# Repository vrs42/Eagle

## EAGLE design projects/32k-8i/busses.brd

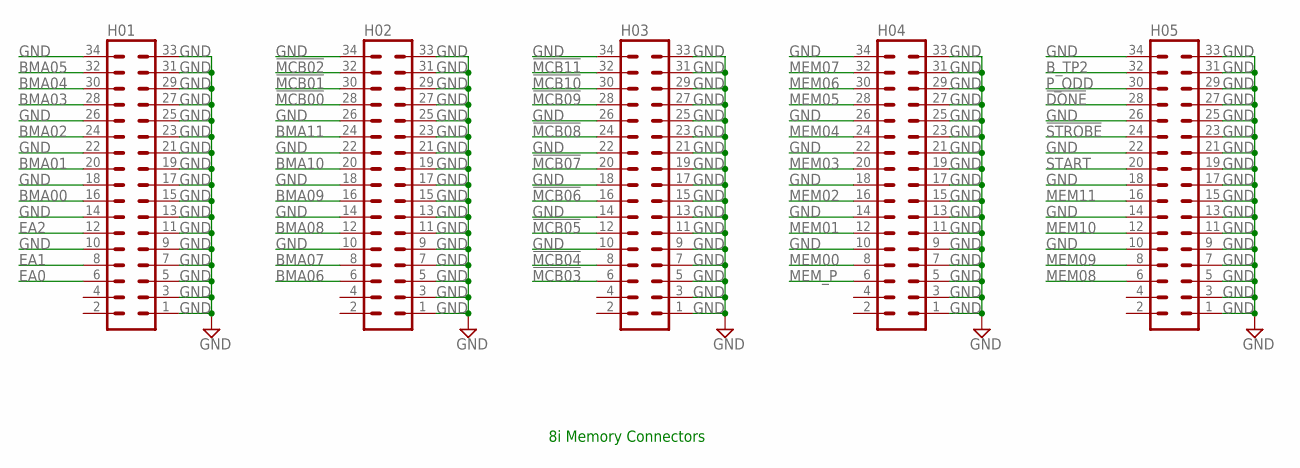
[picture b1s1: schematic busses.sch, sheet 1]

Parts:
H01, H02, H03, H04, H05: MA17-2

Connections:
!DONE: H05.28
!MCB00: H02.28; also elsewhere on the board
!MCB01: H02.30; also elsewhere on the board
!MCB02: H02.32; also elsewhere on the board
!MCB03: H03.6; also elsewhere on the board
!MCB04: H03.8; also elsewhere on the board
!MCB05: H03.12; also elsewhere on the board
!MCB06: H03.16; also elsewhere on the board
!MCB07: H03.20; also elsewhere on the board
!MCB08: H03.24; also elsewhere on the board
!MCB09: H03.28; also elsewhere on the board
!MCB10: H03.30; also elsewhere on the board
!MCB11: H03.32; also elsewhere on the board
!STROBE: H05.24
BMA00: H01.16
BMA01: H01.20
BMA02: H01.24
BMA03: H01.28
BMA04: H01.30
BMA05: H01.32
BMA06: H02.6
BMA07: H02.8
BMA08: H02.12
BMA09: H02.16
BMA10: H02.20
BMA11: H02.24
B_TP2: H05.32
EA0: H01.6; also elsewhere on the board
EA1: H01.8; also elsewhere on the board
EA2: H01.12; also elsewhere on the board
GND: H01.1, H01.3, H01.5, H01.7, H01.9, H01.10, H01.11, H01.13, H01.14, H01.15, H01.17, H01.18, H01.19, H01.21, H01.22, H01.23, H01.25, H01.26, H01.27, H01.29, H01.31, H01.33, H01.34, H02.1, H02.3, H02.5, H02.7, H02.9, H02.10, H02.11, H02.13, H02.14, H02.15, H02.17, H02.18, H02.19, H02.21, H02.22, H02.23, H02.25, H02.26, H02.27, H02.29, H02.31, H02.33, H02.34, H03.1, H03.3, H03.5, H03.7, H03.9, H03.10, H03.11, H03.13, H03.14, H03.15, H03.17, H03.18, H03.19, H03.21, H03.22, H03.23, H03.25, H03.26, H03.27, H03.29, H03.31, H03.33, H03.34, H04.1, H04.3, H04.5, H04.7, H04.9, H04.10, H04.11, H04.13, H04.14, H04.15, H04.17, H04.18, H04.19, H04.21, H04.22, H04.23, H04.25, H04.26, H04.27, H04.29, H04.31, H04.33, H04.34, H05.1, H05.3, H05.5, H05.7, H05.9, H05.10, H05.11, H05.13, H05.14, H05.15, H05.17, H05.18, H05.19, H05.21, H05.22, H05.23, H05.25, H05.26, H05.27, H05.29, H05.31, H05.33, H05.34; also elsewhere on the board
MEM00: H04.8; also elsewhere on the board
MEM01: H04.12; also elsewhere on the board
MEM02: H04.16; also elsewhere on the board
MEM03: H04.20; also elsewhere on the board
MEM04: H04.24; also elsewhere on the board
MEM05: H04.28; also elsewhere on the board
MEM06: H04.30; also elsewhere on the board
MEM07: H04.32; also elsewhere on the board
MEM08: H05.6; also elsewhere on the board
MEM09: H05.8; also elsewhere on the board
MEM10: H05.12; also elsewhere on the board
MEM11: H05.16; also elsewhere on the board
MEM_P: H04.6
P_ODD: H05.30
START: H05.20

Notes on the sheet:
8i Memory Connectors

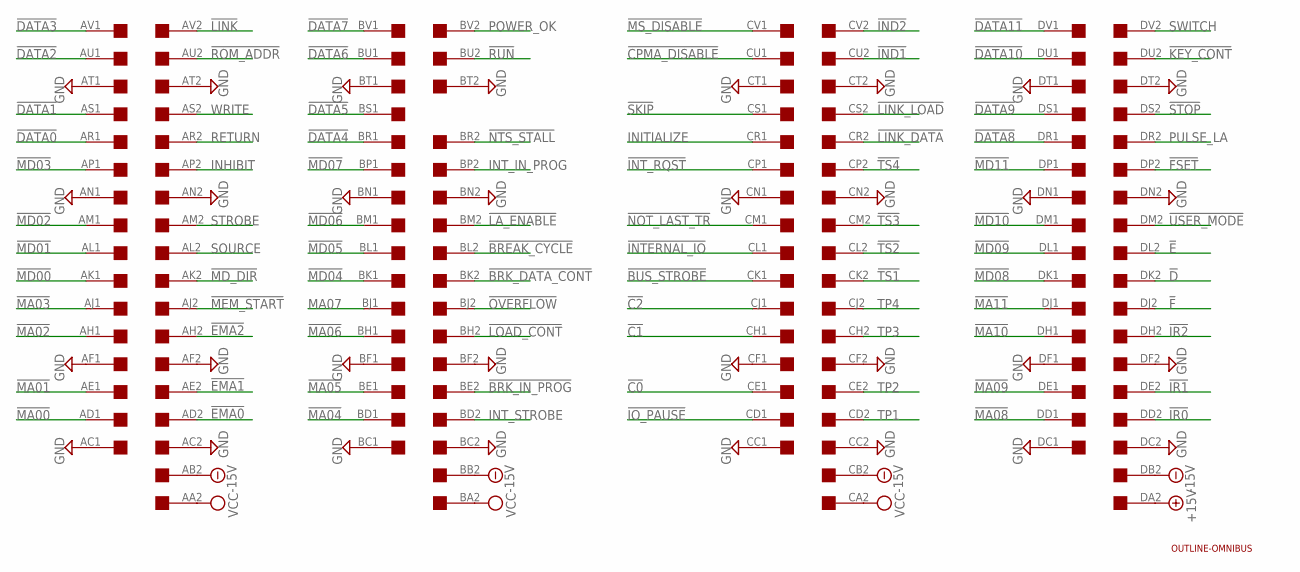
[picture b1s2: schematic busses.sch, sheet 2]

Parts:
U$1: OUTLINE-OMNIBUS; OMNIBUS
U$2: QUAD; EDGE-CON8

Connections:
!BREAK_CYCLE: U$2.BL2
!BRK_DATA_CONT: U$2.BK2
!BRK_IN_PROG: U$2.BE2
!BUS_STROBE: U$2.CK1
!C0: U$2.CE1
!C1: U$2.CH1
!C2: U$2.CJ1
!CPMA_DISABLE: U$2.CU1
!D: U$2.DK2
!DATA0: U$2.AR1
!DATA1: U$2.AS1
!DATA2: U$2.AU1
!DATA3: U$2.AV1
!DATA4: U$2.BR1
!DATA5: U$2.BS1
!DATA6: U$2.BU1
!DATA7: U$2.BV1
!DATA8: U$2.DR1
!DATA9: U$2.DS1
!DATA10: U$2.DU1
!DATA11: U$2.DV1
!E: U$2.DL2
!EMA0: U$2.AD2
!EMA1: U$2.AE2
!EMA2: U$2.AH2
!F: U$2.DJ2
!FSET: U$2.DP2
!IND1: U$2.CU2
!IND2: U$2.CV2
!INTERNAL_IO: U$2.CL1
!INT_RQST: U$2.CP1
!IO_PAUSE: U$2.CD1
!IR0: U$2.DD2
!IR1: U$2.DE2
!IR2: U$2.DH2
!KEY_CONT: U$2.DU2
!LA_ENABLE: U$2.BM2
!LINK: U$2.AV2
!LINK_DATA: U$2.CR2
!LINK_LOAD: U$2.CS2
!LOAD_CONT: U$2.BH2
!MA00: U$2.AD1
!MA01: U$2.AE1
!MA02: U$2.AH1
!MA03: U$2.AJ1
!MA04: U$2.BD1
!MA05: U$2.BE1
!MA06: U$2.BH1
!MA08: U$2.DD1
!MA09: U$2.DE1
!MA10: U$2.DH1
!MA11: U$2.DJ1
!MD00: U$2.AK1; also elsewhere on the board
!MD01: U$2.AL1; also elsewhere on the board
!MD02: U$2.AM1; also elsewhere on the board
!MD03: U$2.AP1; also elsewhere on the board
!MD04: U$2.BK1; also elsewhere on the board
!MD05: U$2.BL1; also elsewhere on the board
!MD06: U$2.BM1; also elsewhere on the board
!MD07: U$2.BP1; also elsewhere on the board
!MD08: U$2.DK1; also elsewhere on the board
!MD09: U$2.DL1; also elsewhere on the board
!MD10: U$2.DM1; also elsewhere on the board
!MD11: U$2.DP1; also elsewhere on the board
!MD_DIR: U$2.AK2; also elsewhere on the board
!MEM_START: U$2.AJ2
!MS_DISABLE: U$2.CV1
!NOT_LAST_TR: U$2.CM1
!NTS_STALL: U$2.BR2
!OVERFLOW: U$2.BJ2
!ROM_ADDR: U$2.AU2
!RUN: U$2.BU2
!SKIP: U$2.CS1
!STOP: U$2.DS2
!TS1: U$2.CK2
!TS2: U$2.CL2
!TS3: U$2.CM2
!TS4: U$2.CP2
!USER_MODE: U$2.DM2
+15V: U$2.DA2
-15V: U$2.AB2, U$2.BB2, U$2.CB2, U$2.DB2
GND: U$2.AC1, U$2.AC2, U$2.AF1, U$2.AF2, U$2.AN1, U$2.AN2, U$2.AT1, U$2.AT2, U$2.BC1, U$2.BC2, U$2.BF1, U$2.BF2, U$2.BN1, U$2.BN2, U$2.BT1, U$2.BT2, U$2.CC1, U$2.CC2, U$2.CF1, U$2.CF2, U$2.CN1, U$2.CN2, U$2.CT1, U$2.CT2, U$2.DC1, U$2.DC2, U$2.DF1, U$2.DF2, U$2.DN1, U$2.DN2, U$2.DT1, U$2.DT2; also elsewhere on the board
INHIBIT: U$2.AP2
INITIALIZE: U$2.CR1
INT_IN_PROG: U$2.BP2
INT_STROBE: U$2.BD2
MA07: U$2.BJ1
POWER_OK: U$2.BV2
PULSE_LA: U$2.DR2
RETURN: U$2.AR2
SOURCE: U$2.AL2
STROBE: U$2.AM2
SWITCH: U$2.DV2
TP1: U$2.CD2
TP2: U$2.CE2
TP3: U$2.CH2
TP4: U$2.CJ2
VCC: U$2.AA2, U$2.BA2, U$2.CA2; also elsewhere on the board
WRITE: U$2.AS2

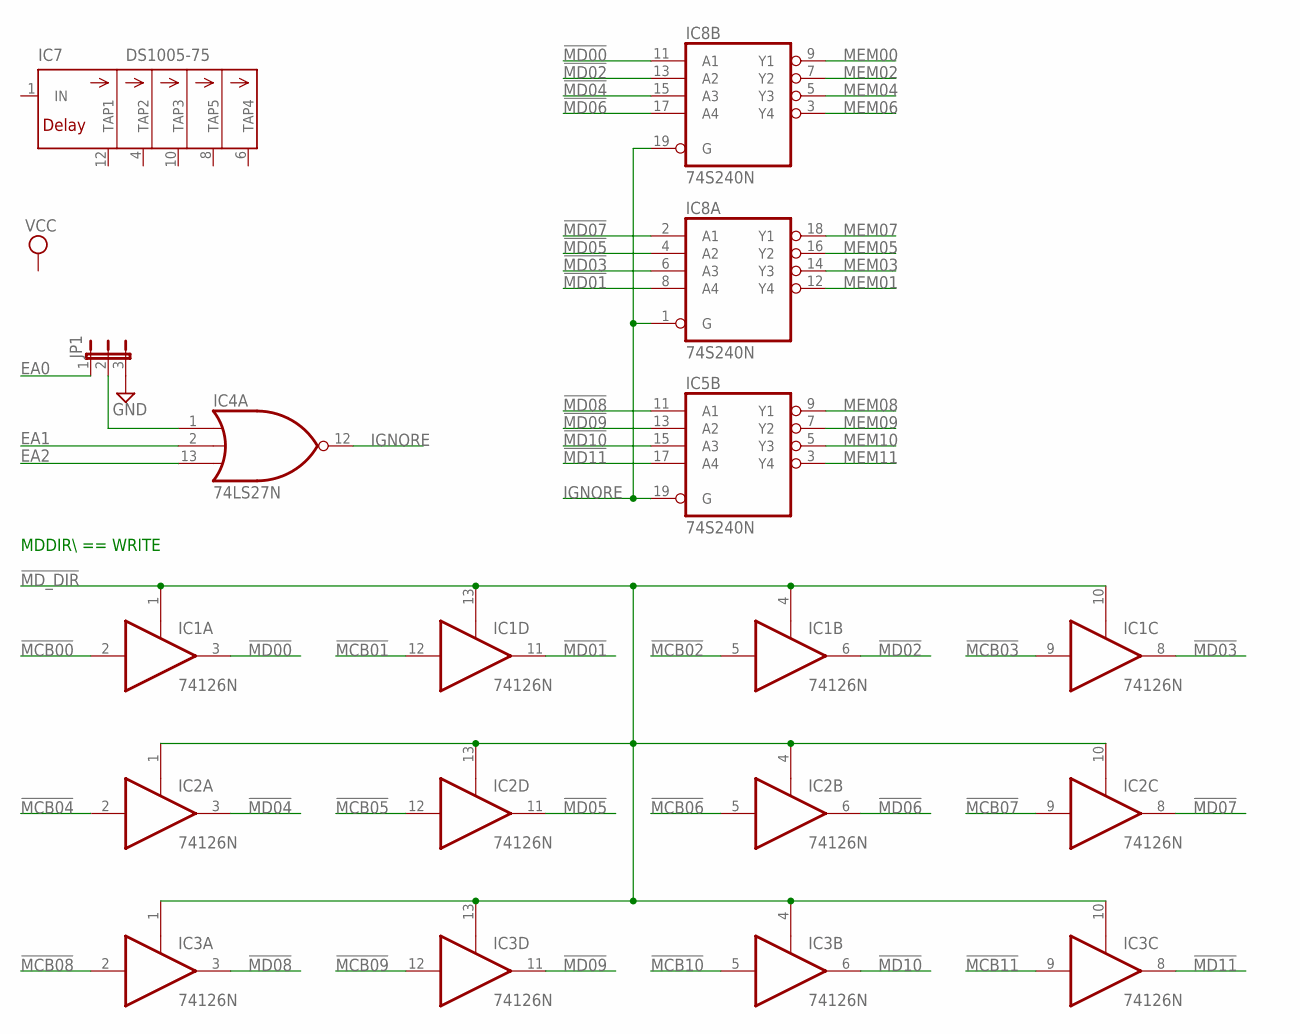
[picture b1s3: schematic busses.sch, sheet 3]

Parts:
IC1, IC2, IC3: 74126N; DIL14
IC4: 74LS27N; DIL14
IC5, IC8: 74S240N; DIL20
IC7: DS1005-75; DIL14
JP1: JP2E; JP2

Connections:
!MCB00: IC1.2 (I); also elsewhere on the board
!MCB01: IC1.12 (I); also elsewhere on the board
!MCB02: IC1.5 (I); also elsewhere on the board
!MCB03: IC1.9 (I); also elsewhere on the board
!MCB04: IC2.2 (I); also elsewhere on the board
!MCB05: IC2.12 (I); also elsewhere on the board
!MCB06: IC2.5 (I); also elsewhere on the board
!MCB07: IC2.9 (I); also elsewhere on the board
!MCB08: IC3.2 (I); also elsewhere on the board
!MCB09: IC3.12 (I); also elsewhere on the board
!MCB10: IC3.5 (I); also elsewhere on the board
!MCB11: IC3.9 (I); also elsewhere on the board
!MD00: IC1.3 (O), IC8.11 (A1); also elsewhere on the board
!MD01: IC1.11 (O), IC8.8 (A4); also elsewhere on the board
!MD02: IC1.6 (O), IC8.13 (A2); also elsewhere on the board
!MD03: IC1.8 (O), IC8.6 (A3); also elsewhere on the board
!MD04: IC2.3 (O), IC8.15 (A3); also elsewhere on the board
!MD05: IC2.11 (O), IC8.4 (A2); also elsewhere on the board
!MD06: IC2.6 (O), IC8.17 (A4); also elsewhere on the board
!MD07: IC2.8 (O), IC8.2 (A1); also elsewhere on the board
!MD08: IC3.3 (O), IC5.11 (A1); also elsewhere on the board
!MD09: IC3.11 (O), IC5.13 (A2); also elsewhere on the board
!MD10: IC3.6 (O), IC5.15 (A3); also elsewhere on the board
!MD11: IC3.8 (O), IC5.17 (A4); also elsewhere on the board
!MD_DIR: IC1.1 (OE), IC1.4 (OE), IC1.10 (OE), IC1.13 (OE), IC2.1 (OE), IC2.4 (OE), IC2.10 (OE), IC2.13 (OE), IC3.1 (OE), IC3.4 (OE), IC3.10 (OE), IC3.13 (OE); also elsewhere on the board
EA0: JP1.1; also elsewhere on the board
EA1: IC4.2 (I1); also elsewhere on the board
EA2: IC4.13 (I2); also elsewhere on the board
GND: IC1.7 (GND), IC2.7 (GND), IC3.7 (GND), IC4.7 (GND), IC5.10 (GND), IC7.7 (GND), IC8.10 (GND), JP1.3; also elsewhere on the board
IGNORE: IC4.12 (O), IC5.19 (G), IC8.1 (G), IC8.19 (G)
MEM00: IC8.9 (Y1); also elsewhere on the board
MEM01: IC8.12 (Y4); also elsewhere on the board
MEM02: IC8.7 (Y2); also elsewhere on the board
MEM03: IC8.14 (Y3); also elsewhere on the board
MEM04: IC8.5 (Y3); also elsewhere on the board
MEM05: IC8.16 (Y2); also elsewhere on the board
MEM06: IC8.3 (Y4); also elsewhere on the board
MEM07: IC8.18 (Y1); also elsewhere on the board
MEM08: IC5.9 (Y1); also elsewhere on the board
MEM09: IC5.7 (Y2); also elsewhere on the board
MEM10: IC5.5 (Y3); also elsewhere on the board
MEM11: IC5.3 (Y4); also elsewhere on the board
unnamed: IC4.1 (I0), JP1.2
VCC: IC1.14 (VCC), IC2.14 (VCC), IC3.14 (VCC), IC4.14 (VCC), IC5.20 (VCC), IC7.14 (VCC), IC8.20 (VCC); also elsewhere on the board

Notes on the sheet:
MDDIR\\ == WRITE

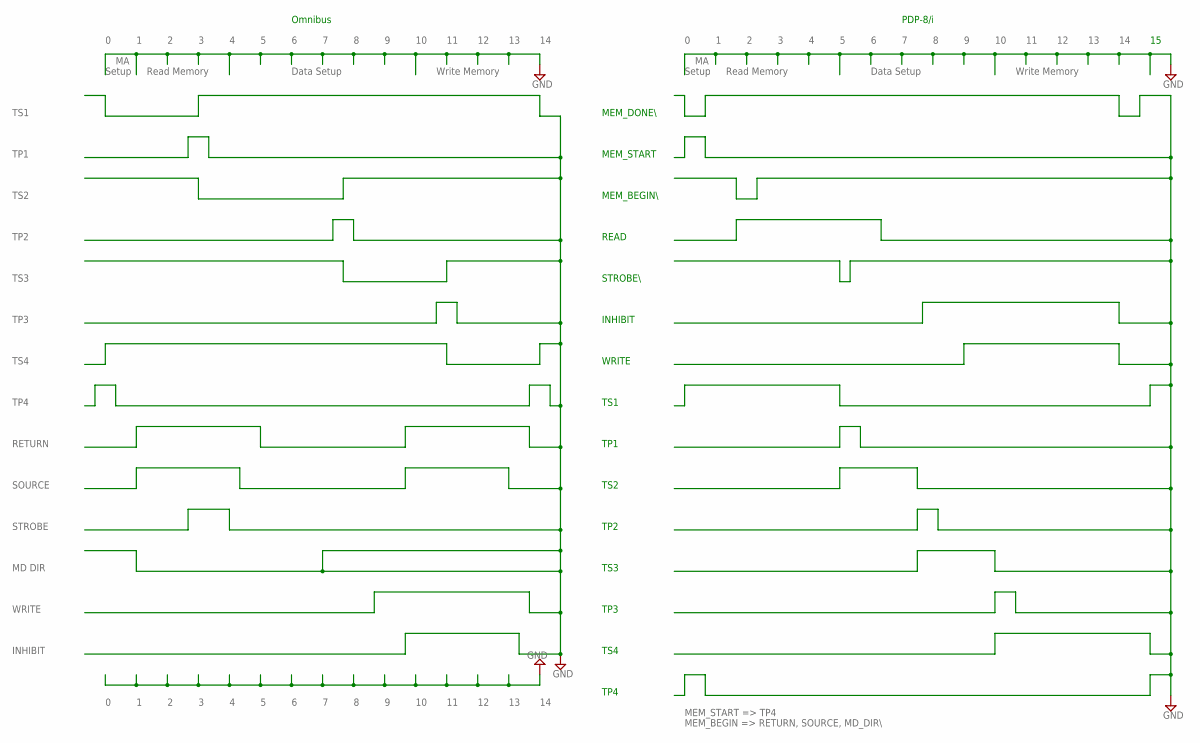
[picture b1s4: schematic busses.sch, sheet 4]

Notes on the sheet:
MEM_DONE\\
MEM_START
MEM_BEGIN\\
READ
STROBE\\
INHIBIT
WRITE
TS1
TS2
TS3
TS4
TP1
TP2
TP3
TP4
STROBE
SOURCE
RETURN
MD DIR
Setup
Read Memory
Data Setup
Write Memory
MEM_START => TP4
MEM_BEGIN => RETURN, SOURCE, MD_DIR\\
Omnibus
PDP-8/i

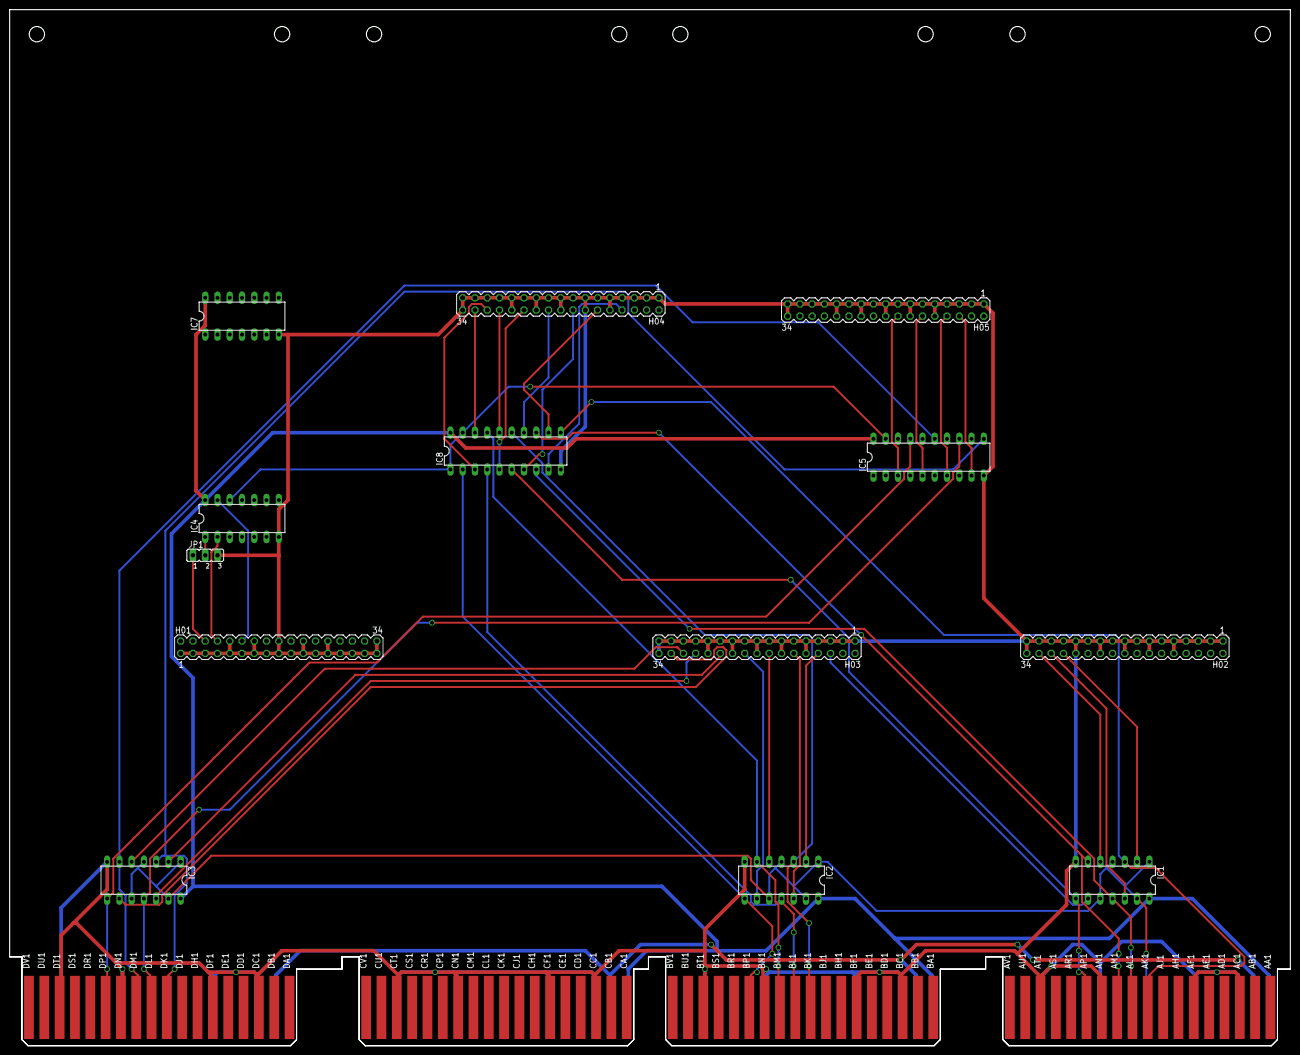
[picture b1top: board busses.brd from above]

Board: 2 copper layers, 265.3 x 214.6 mm, 15 parts (0 on the bottom side), 45 nets.

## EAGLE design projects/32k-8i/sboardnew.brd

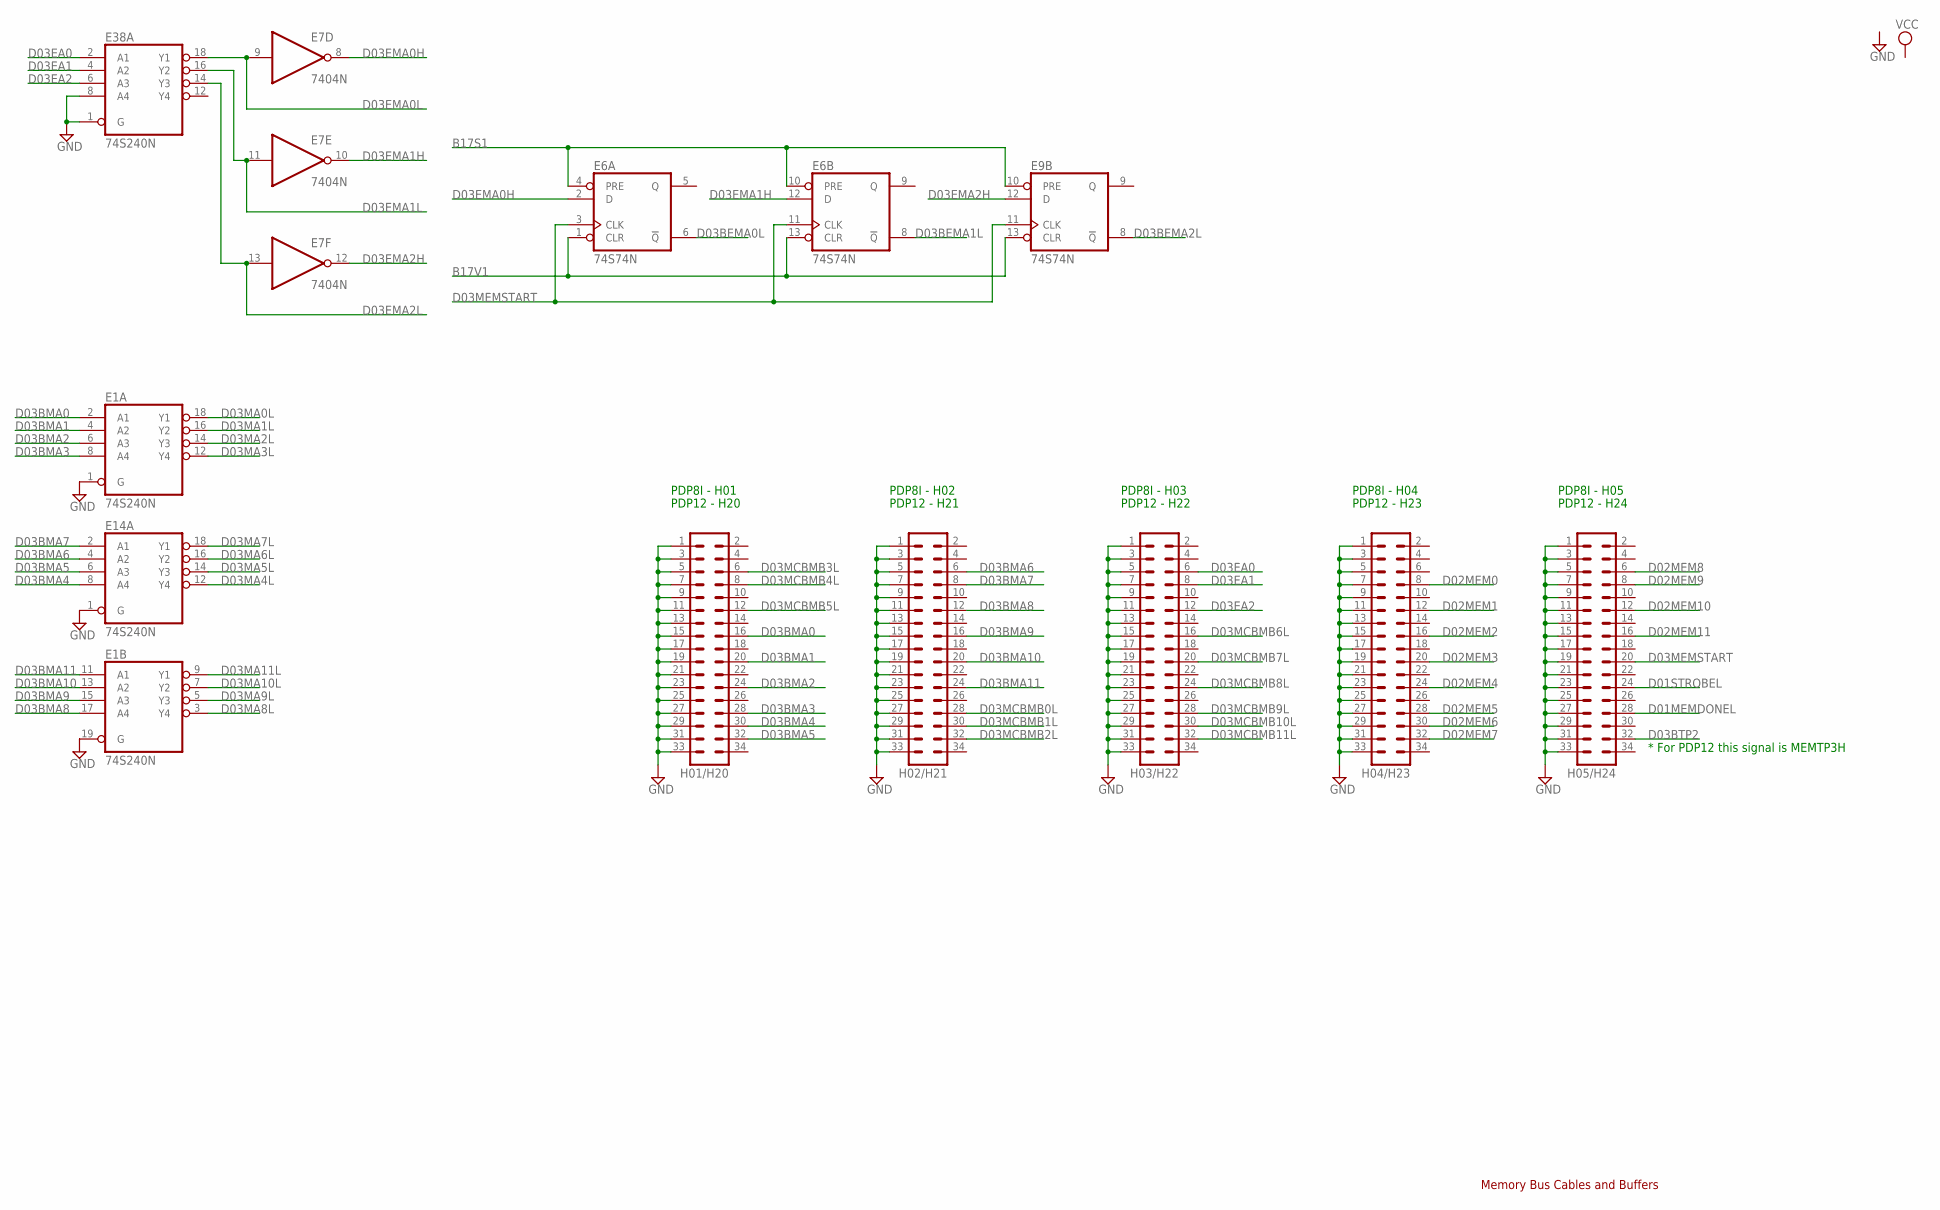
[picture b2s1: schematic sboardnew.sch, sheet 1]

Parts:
E1, E14, E38: 74S240N; DIL20
E6, E9: 74S74N; DIL14
E7: 7404N; DIL14
H01/H20, H02/H21, H03/H22, H04/H23, H05/H24: MA17-2

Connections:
B17S1: E6.4 (PRE), E6.10 (PRE), E9.10 (PRE); also elsewhere on the board
B17V1: E6.1 (CLR), E6.13 (CLR), E9.13 (CLR); also elsewhere on the board
D01MEMDONEL: H05/H24.28; also elsewhere on the board
D01STROBEL: H05/H24.24; also elsewhere on the board
D02MEM0: H04/H23.8; also elsewhere on the board
D02MEM1: H04/H23.12; also elsewhere on the board
D02MEM2: H04/H23.16; also elsewhere on the board
D02MEM3: H04/H23.20; also elsewhere on the board
D02MEM4: H04/H23.24; also elsewhere on the board
D02MEM5: H04/H23.28; also elsewhere on the board
D02MEM6: H04/H23.30; also elsewhere on the board
D02MEM7: H04/H23.32; also elsewhere on the board
D02MEM8: H05/H24.6; also elsewhere on the board
D02MEM9: H05/H24.8; also elsewhere on the board
D02MEM10: H05/H24.12; also elsewhere on the board
D02MEM11: H05/H24.16; also elsewhere on the board
D03BEMA0L: E6.6 (!Q); also elsewhere on the board
D03BEMA1L: E6.8 (!Q); also elsewhere on the board
D03BEMA2L: E9.8 (!Q); also elsewhere on the board
D03BMA0: E1.2 (A1), H01/H20.16
D03BMA1: E1.4 (A2), H01/H20.20
D03BMA2: E1.6 (A3), H01/H20.24
D03BMA3: E1.8 (A4), H01/H20.28
D03BMA4: E14.8 (A4), H01/H20.30
D03BMA5: E14.6 (A3), H01/H20.32
D03BMA6: E14.4 (A2), H02/H21.6
D03BMA7: E14.2 (A1), H02/H21.8
D03BMA8: E1.17 (A4), H02/H21.12
D03BMA9: E1.15 (A3), H02/H21.16
D03BMA10: E1.13 (A2), H02/H21.20
D03BMA11: E1.11 (A1), H02/H21.24
D03BTP2: H05/H24.32; also elsewhere on the board
D03EA0: E38.2 (A1), H03/H22.6
D03EA1: E38.4 (A2), H03/H22.8
D03EA2: E38.6 (A3), H03/H22.12
D03EMA0H: E6.2 (D), E7.8 (O); also elsewhere on the board
D03EMA0L: E7.9 (I), E38.18 (Y1); also elsewhere on the board
D03EMA1H: E6.12 (D), E7.10 (O); also elsewhere on the board
D03EMA1L: E7.11 (I), E38.16 (Y2); also elsewhere on the board
D03EMA2H: E7.12 (O), E9.12 (D); also elsewhere on the board
D03EMA2L: E7.13 (I), E38.14 (Y3); also elsewhere on the board
D03MA0L: E1.18 (Y1); also elsewhere on the board
D03MA1L: E1.16 (Y2); also elsewhere on the board
D03MA2L: E1.14 (Y3); also elsewhere on the board
D03MA3L: E1.12 (Y4); also elsewhere on the board
D03MA4L: E14.12 (Y4); also elsewhere on the board
D03MA5L: E14.14 (Y3); also elsewhere on the board
D03MA6L: E14.16 (Y2); also elsewhere on the board
D03MA7L: E14.18 (Y1); also elsewhere on the board
D03MA8L: E1.3 (Y4); also elsewhere on the board
D03MA9L: E1.5 (Y3); also elsewhere on the board
D03MA10L: E1.7 (Y2); also elsewhere on the board
D03MA11L: E1.9 (Y1); also elsewhere on the board
D03MCBMB0L: H02/H21.28; also elsewhere on the board
D03MCBMB1L: H02/H21.30; also elsewhere on the board
D03MCBMB2L: H02/H21.32; also elsewhere on the board
D03MCBMB3L: H01/H20.6; also elsewhere on the board
D03MCBMB4L: H01/H20.8; also elsewhere on the board
D03MCBMB5L: H01/H20.12; also elsewhere on the board
D03MCBMB6L: H03/H22.16; also elsewhere on the board
D03MCBMB7L: H03/H22.20; also elsewhere on the board
D03MCBMB8L: H03/H22.24; also elsewhere on the board
D03MCBMB9L: H03/H22.28; also elsewhere on the board
D03MCBMB10L: H03/H22.30; also elsewhere on the board
D03MCBMB11L: H03/H22.32; also elsewhere on the board
D03MEMSTART: E6.3 (CLK), E6.11 (CLK), E9.11 (CLK), H05/H24.20; also elsewhere on the board
GND: E1.1 (G), E1.10 (GND), E1.19 (G), E6.7 (GND), E7.7 (GND), E9.7 (GND), E14.1 (G), E14.10 (GND), E38.1 (G), E38.8 (A4), E38.10 (GND), H01/H20.1, H01/H20.3, H01/H20.5, H01/H20.7, H01/H20.9, H01/H20.11, H01/H20.13, H01/H20.15, H01/H20.17, H01/H20.19, H01/H20.21, H01/H20.23, H01/H20.25, H01/H20.27, H01/H20.29, H01/H20.31, H01/H20.33, H02/H21.1, H02/H21.3, H02/H21.5, H02/H21.7, H02/H21.9, H02/H21.11, H02/H21.13, H02/H21.15, H02/H21.17, H02/H21.19, H02/H21.21, H02/H21.23, H02/H21.25, H02/H21.27, H02/H21.29, H02/H21.31, H02/H21.33, H03/H22.1, H03/H22.3, H03/H22.5, H03/H22.7, H03/H22.9, H03/H22.11, H03/H22.13, H03/H22.15, H03/H22.17, H03/H22.19, H03/H22.21, H03/H22.23, H03/H22.25, H03/H22.27, H03/H22.29, H03/H22.31, H03/H22.33, H04/H23.1, H04/H23.3, H04/H23.5, H04/H23.7, H04/H23.9, H04/H23.11, H04/H23.13, H04/H23.15, H04/H23.17, H04/H23.19, H04/H23.21, H04/H23.23, H04/H23.25, H04/H23.27, H04/H23.29, H04/H23.31, H04/H23.33, H05/H24.1, H05/H24.3, H05/H24.5, H05/H24.7, H05/H24.9, H05/H24.11, H05/H24.13, H05/H24.15, H05/H24.17, H05/H24.19, H05/H24.21, H05/H24.23, H05/H24.25, H05/H24.27, H05/H24.29, H05/H24.31, H05/H24.33; also elsewhere on the board
VCC: E1.20 (VCC), E6.14 (VCC), E7.14 (VCC), E9.14 (VCC), E14.20 (VCC), E38.20 (VCC); also elsewhere on the board

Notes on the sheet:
Memory Bus Cables and Buffers
* For PDP12 this signal is MEMTP3H
PDP8I - H01
PDP8I - H02
PDP8I - H03
PDP8I - H04
PDP8I - H05
PDP12 - H20
PDP12 - H21
PDP12 - H22
PDP12 - H23
PDP12 - H24

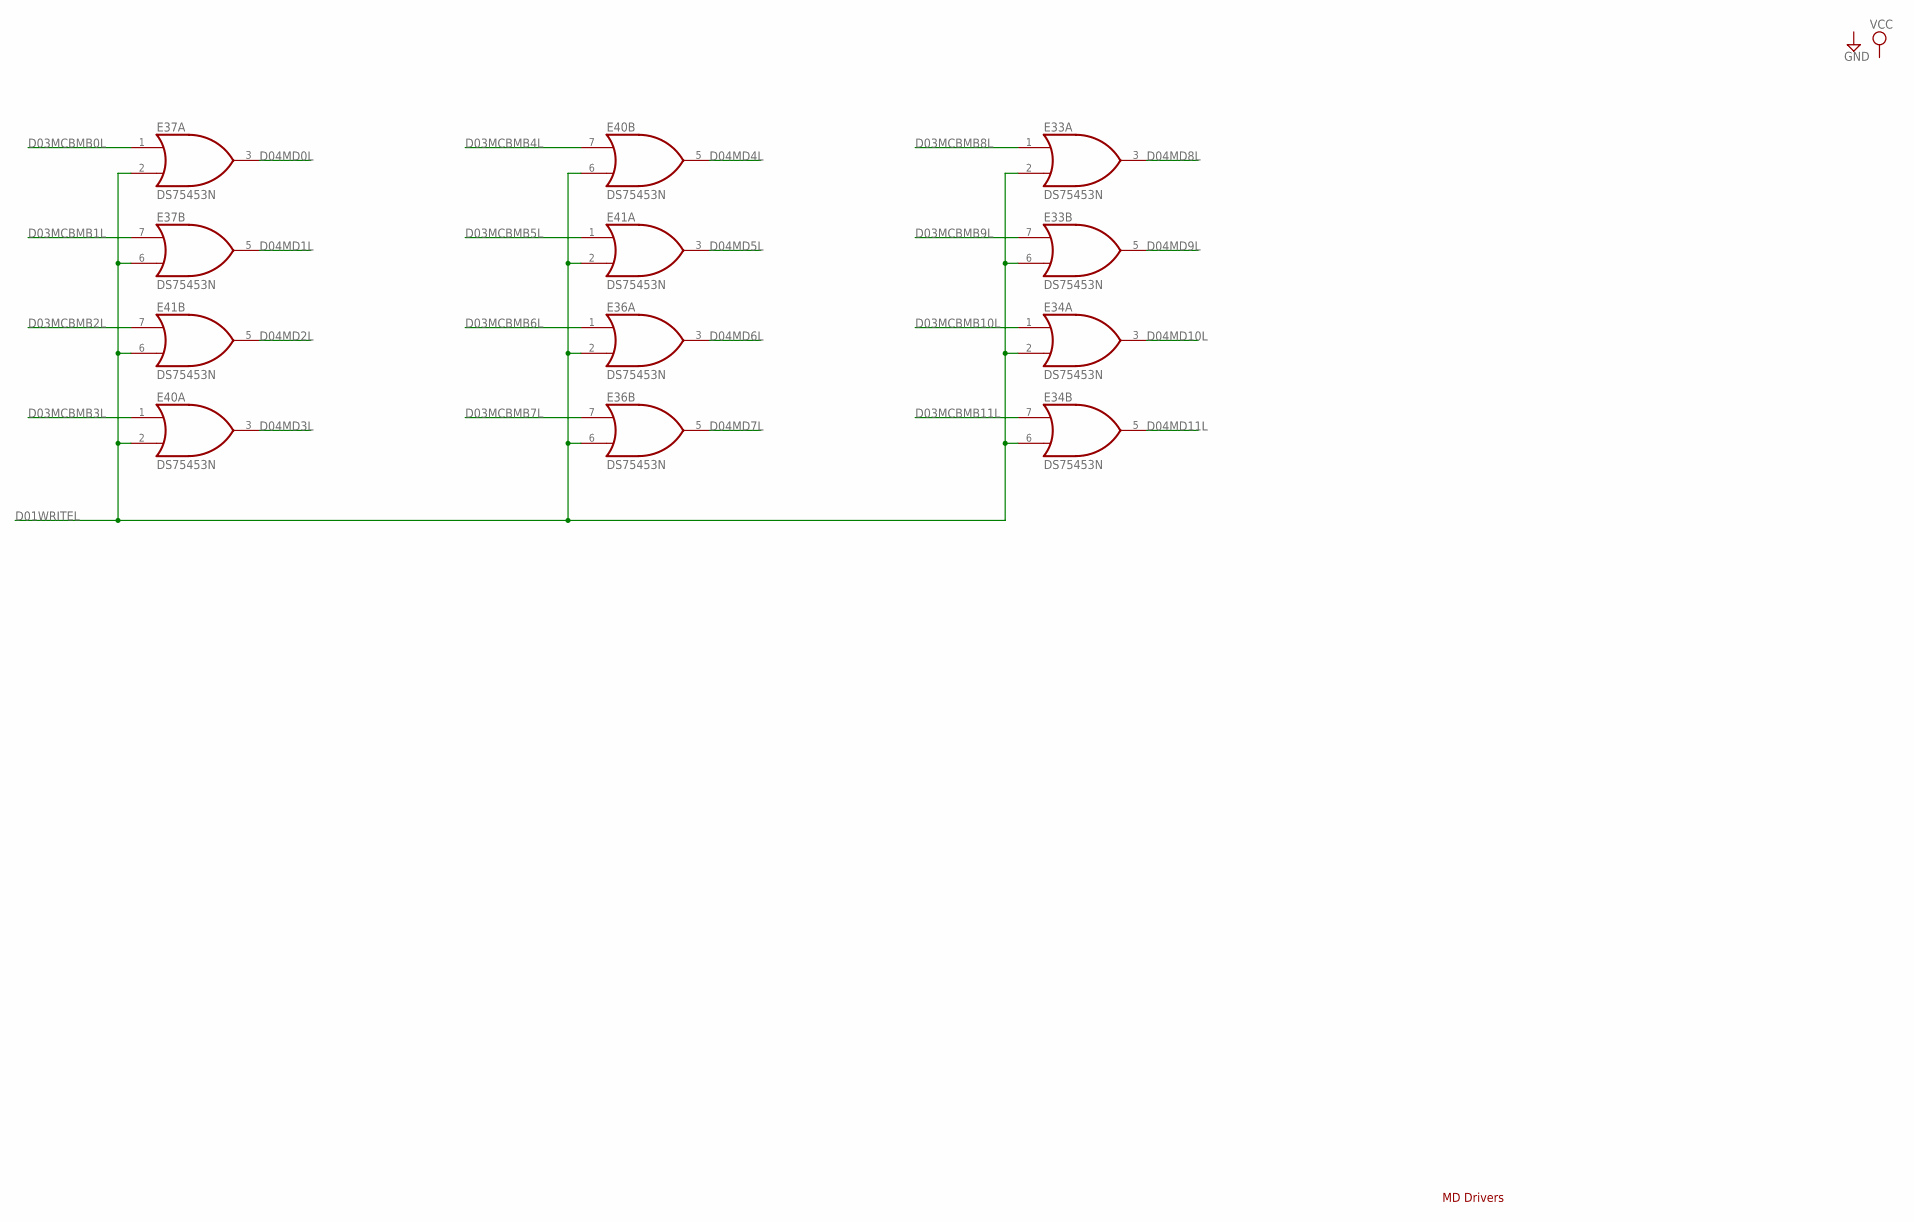
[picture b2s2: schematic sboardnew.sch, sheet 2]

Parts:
E33, E34, E36, E37, E40, E41: DS75453N; DIL08

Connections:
D01WRITEL: E33.2 (I1), E33.6 (I1), E34.2 (I1), E34.6 (I1), E36.2 (I1), E36.6 (I1), E37.2 (I1), E37.6 (I1), E40.2 (I1), E40.6 (I1), E41.2 (I1), E41.6 (I1); also elsewhere on the board
D03MCBMB0L: E37.1 (I0); also elsewhere on the board
D03MCBMB1L: E37.7 (I0); also elsewhere on the board
D03MCBMB2L: E41.7 (I0); also elsewhere on the board
D03MCBMB3L: E40.1 (I0); also elsewhere on the board
D03MCBMB4L: E40.7 (I0); also elsewhere on the board
D03MCBMB5L: E41.1 (I0); also elsewhere on the board
D03MCBMB6L: E36.1 (I0); also elsewhere on the board
D03MCBMB7L: E36.7 (I0); also elsewhere on the board
D03MCBMB8L: E33.1 (I0); also elsewhere on the board
D03MCBMB9L: E33.7 (I0); also elsewhere on the board
D03MCBMB10L: E34.1 (I0); also elsewhere on the board
D03MCBMB11L: E34.7 (I0); also elsewhere on the board
D04MD0L: E37.3 (O); also elsewhere on the board
D04MD1L: E37.5 (O); also elsewhere on the board
D04MD2L: E41.5 (O); also elsewhere on the board
D04MD3L: E40.3 (O); also elsewhere on the board
D04MD4L: E40.5 (O); also elsewhere on the board
D04MD5L: E41.3 (O); also elsewhere on the board
D04MD6L: E36.3 (O); also elsewhere on the board
D04MD7L: E36.5 (O); also elsewhere on the board
D04MD8L: E33.3 (O); also elsewhere on the board
D04MD9L: E33.5 (O); also elsewhere on the board
D04MD10L: E34.3 (O); also elsewhere on the board
D04MD11L: E34.5 (O); also elsewhere on the board
GND: E33.4 (GND), E34.4 (GND), E36.4 (GND), E37.4 (GND), E40.4 (GND), E41.4 (GND); also elsewhere on the board
VCC: E33.8 (VCC), E34.8 (VCC), E36.8 (VCC), E37.8 (VCC), E40.8 (VCC), E41.8 (VCC); also elsewhere on the board

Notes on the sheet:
MD Drivers

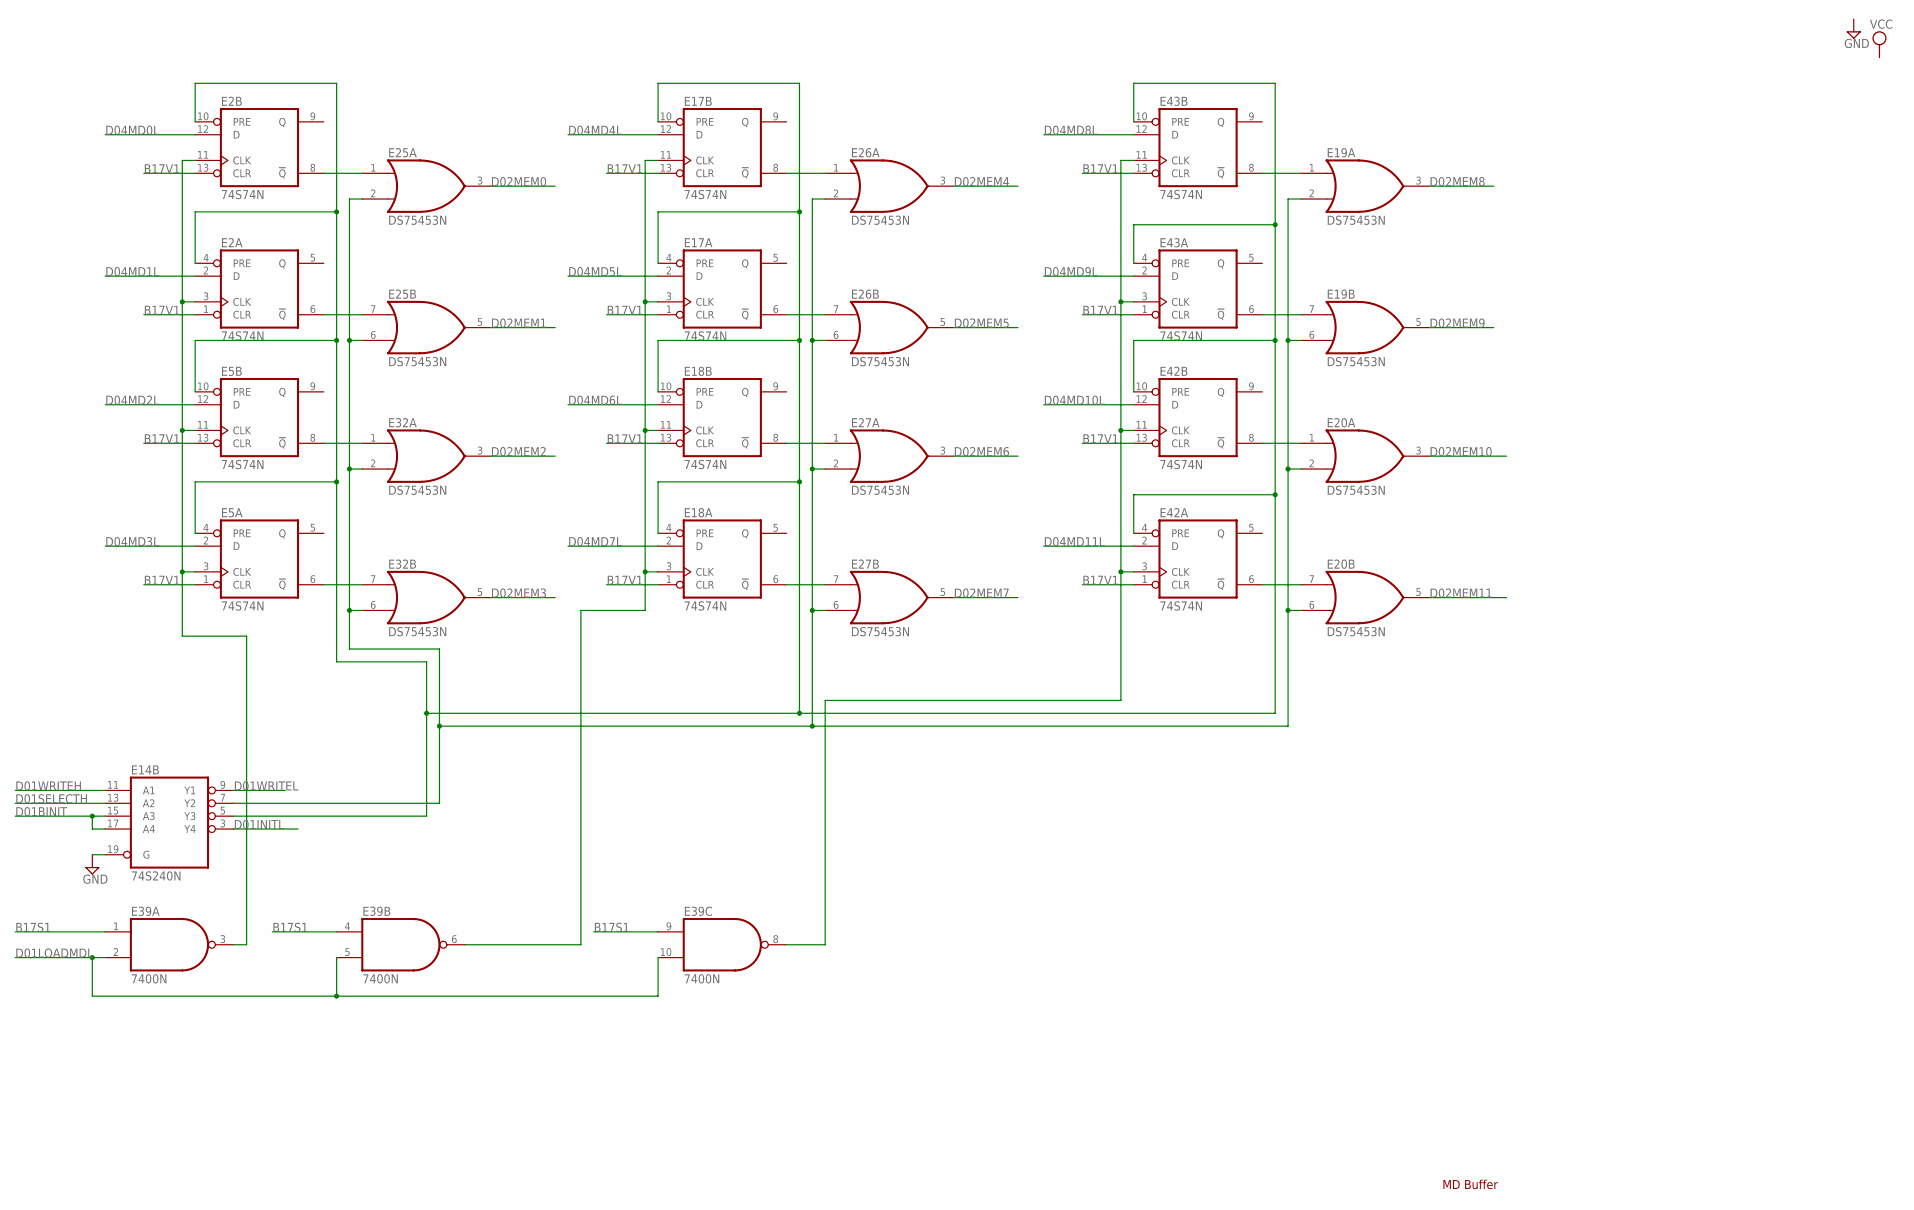
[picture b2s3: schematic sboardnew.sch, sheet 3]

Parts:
E2, E5, E17, E18, E42, E43: 74S74N; DIL14
E14: 74S240N; DIL20
E19, E20, E25, E26, E27, E32: DS75453N; DIL08
E39: 7400N; DIL14

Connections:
B17S1: E39.1 (I0), E39.4 (I0), E39.9 (I0); also elsewhere on the board
B17V1: E2.1 (CLR), E2.13 (CLR), E5.1 (CLR), E5.13 (CLR), E17.1 (CLR), E17.13 (CLR), E18.1 (CLR), E18.13 (CLR), E42.1 (CLR), E42.13 (CLR), E43.1 (CLR), E43.13 (CLR); also elsewhere on the board
D01BINIT: E14.15 (A3), E14.17 (A4); also elsewhere on the board
D01INITL: E14.3 (Y4); also elsewhere on the board
D01LOADMDL: E39.2 (I1), E39.5 (I1), E39.10 (I1); also elsewhere on the board
D01SELECTH: E14.13 (A2); also elsewhere on the board
D01WRITEH: E14.11 (A1); also elsewhere on the board
D01WRITEL: E14.9 (Y1); also elsewhere on the board
D02MEM0: E25.3 (O); also elsewhere on the board
D02MEM1: E25.5 (O); also elsewhere on the board
D02MEM2: E32.3 (O); also elsewhere on the board
D02MEM3: E32.5 (O); also elsewhere on the board
D02MEM4: E26.3 (O); also elsewhere on the board
D02MEM5: E26.5 (O); also elsewhere on the board
D02MEM6: E27.3 (O); also elsewhere on the board
D02MEM7: E27.5 (O); also elsewhere on the board
D02MEM8: E19.3 (O); also elsewhere on the board
D02MEM9: E19.5 (O); also elsewhere on the board
D02MEM10: E20.3 (O); also elsewhere on the board
D02MEM11: E20.5 (O); also elsewhere on the board
D04MD0L: E2.12 (D); also elsewhere on the board
D04MD1L: E2.2 (D); also elsewhere on the board
D04MD2L: E5.12 (D); also elsewhere on the board
D04MD3L: E5.2 (D); also elsewhere on the board
D04MD4L: E17.12 (D); also elsewhere on the board
D04MD5L: E17.2 (D); also elsewhere on the board
D04MD6L: E18.12 (D); also elsewhere on the board
D04MD7L: E18.2 (D); also elsewhere on the board
D04MD8L: E43.12 (D); also elsewhere on the board
D04MD9L: E43.2 (D); also elsewhere on the board
D04MD10L: E42.12 (D); also elsewhere on the board
D04MD11L: E42.2 (D); also elsewhere on the board
GND: E2.7 (GND), E5.7 (GND), E14.10 (GND), E14.19 (G), E17.7 (GND), E18.7 (GND), E19.4 (GND), E20.4 (GND), E25.4 (GND), E26.4 (GND), E27.4 (GND), E32.4 (GND), E39.7 (GND), E42.7 (GND), E43.7 (GND); also elsewhere on the board
unnamed: E2.3 (CLK), E2.11 (CLK), E5.3 (CLK), E5.11 (CLK), E39.3 (O)
unnamed: E5.6 (!Q), E32.7 (I0)
unnamed: E2.8 (!Q), E25.1 (I0)
unnamed: E2.6 (!Q), E25.7 (I0)
unnamed: E17.3 (CLK), E17.11 (CLK), E18.3 (CLK), E18.11 (CLK), E39.6 (O)
unnamed: E5.8 (!Q), E32.1 (I0)
unnamed: E2.4 (PRE), E2.10 (PRE), E5.4 (PRE), E5.10 (PRE), E14.5 (Y3), E17.4 (PRE), E17.10 (PRE), E18.4 (PRE), E18.10 (PRE), E42.4 (PRE), E42.10 (PRE), E43.4 (PRE), E43.10 (PRE)
unnamed: E14.7 (Y2), E19.2 (I1), E19.6 (I1), E20.2 (I1), E20.6 (I1), E25.2 (I1), E25.6 (I1), E26.2 (I1), E26.6 (I1), E27.2 (I1), E27.6 (I1), E32.2 (I1), E32.6 (I1)
unnamed: E17.6 (!Q), E26.7 (I0)
unnamed: E18.6 (!Q), E27.7 (I0)
unnamed: E18.8 (!Q), E27.1 (I0)
unnamed: E17.8 (!Q), E26.1 (I0)
unnamed: E20.7 (I0), E42.6 (!Q)
unnamed: E20.1 (I0), E42.8 (!Q)
unnamed: E39.8 (O), E42.3 (CLK), E42.11 (CLK), E43.3 (CLK), E43.11 (CLK)
unnamed: E19.7 (I0), E43.6 (!Q)
unnamed: E19.1 (I0), E43.8 (!Q)
VCC: E2.14 (VCC), E5.14 (VCC), E14.20 (VCC), E17.14 (VCC), E18.14 (VCC), E19.8 (VCC), E20.8 (VCC), E25.8 (VCC), E26.8 (VCC), E27.8 (VCC), E32.8 (VCC), E39.14 (VCC), E42.14 (VCC), E43.14 (VCC); also elsewhere on the board

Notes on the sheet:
MD Buffer
